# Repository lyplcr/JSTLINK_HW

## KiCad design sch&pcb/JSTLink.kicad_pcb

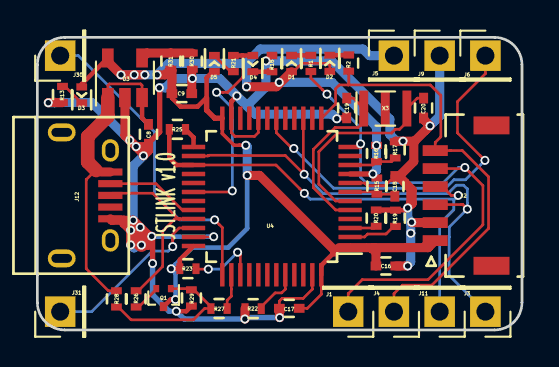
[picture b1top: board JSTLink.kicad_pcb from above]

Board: 2 copper layers, 26.9 x 16.3 mm, 47 parts (1 on the bottom side), 31 nets.

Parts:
C8, C9: 1uF; C_0402
C16, C17: 100nF; C_0402
C18: 10nF; C_0402
C19, C20: 22pF; C_0402
D1, D4: LED-Blue; LED_0402
D2, D5: LED-Green; LED_0402
D3: LED-GREEN; LED_0402
J1, J3, J4, J5, J6, J9, J11, J30, J31: Header_1x1; Pin_Header_Straight_1x01_Pitch2.54mm
J2: JST1.0 1x6; JST_SHL_SM06B-SHLS-TF_06x1.00mm_Angled
J12: USB; USB_Micro-B
LOGO1: LOGO_PINNO_PIC_50x50
Q1: CJ;MMBT3904M; SOT-723
R1, R2, R13, R18, R21: 100k; R_0402
R15, R16, R17, R19, R22, R23, R28: 10k; R_0402
R20: DNP 10k; R_0402
R25, R26, R27: 1k; R_0402
R29: 36k; R_0402
R30, R31: DNP 0R_10nF_RES; R_0402
U3: TPS782; SOT-23-5
U4: STM32F103C8; LQFP-48_7x7mm_Pitch0.5mm
X3: 8MHz; Crystal_SMD_3pin_3.2x1.5mm

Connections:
+3V3: C9.1, C16.1, C17.1, D1.2, D2.2, D3.2, D5.2, J2.1, J5.1, Q1.3, R15.1, R16.2, R23.1, R31.1, U3.5, U4.1, U4.9, U4.24, U4.36, U4.48
/ST-LINK/LED_STLINK: D4.2, R21.2, U4.30
/ST-LINK/NRST: J6.1, U4.18
/ST-LINK/OSC_IN: C19.1, U4.5, X3.1
/ST-LINK/OSC_OUT: C20.1, U4.6, X3.2
/ST-LINK/STM_JTCK: J30.1, U4.37
/ST-LINK/STM_JTMS: J31.1, U4.34
/ST-LINK/STM_RST: C18.1, R15.2, U4.7
/ST-LINK/SWCLK: J2.3, J3.1, U4.15, U4.26
/ST-LINK/SWDIO: J2.4, J11.1, R25.2, U4.27
/ST-LINK/T_SWDIO_IN: R25.1, U4.25
/ST-LINK/USB_DM: J12.2, U4.32
/ST-LINK/USB_DP: J12.3, R26.1, U4.33
/ST-LINK/USB_RENUMn: R27.1, U4.38
/ST-LINK/VBUS: C8.1, J12.1, R28.1, U3.1, U3.3
/ST-LINK/VCP_RX: J1.1, J2.5, R1.2, U4.12
/ST-LINK/VCP_TX: J2.6, J4.1, R2.2, U4.13
GND: C8.2, C9.2, C16.2, C17.2, C18.2, C19.2, C20.2, J2.2, J9.1, J12.5, R13.2, R17.1, R18.2, R19.2, R20.2, R22.1, R29.1, R30.1, U3.2, U4.8, U4.20, U4.23, U4.35, U4.47
unnamed: D1.1, R1.1
unnamed: D2.1, R2.1
unnamed: D3.1, R13.1
unnamed: D4.1, R18.1
unnamed: D5.1, R21.1
unnamed: Q1.1, R27.2, R28.2, R29.2
unnamed: Q1.2, R26.2
unnamed: R16.1, R17.2, U4.10
unnamed: R19.1, U4.2
unnamed: R20.1, U4.3
unnamed: R22.2, U4.44
unnamed: R23.2, U4.39
unnamed: R30.2, R31.2, U3.4

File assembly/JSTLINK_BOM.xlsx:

Id | 代号 | 封装 | 数量 | 名称 | 供应商和REF
1 | C8,C9 | C_0402 | 2 | 1uF
2 | C16,C17 | C_0402 | 2 | 100nF
3 | C18 | C_0402 | 1 | 10nF
4 | C19,C20 | C_0402 | 2 | 22pF
5 | D1,D4 | LED_0402 | 2 | LED-Blue
6 | D2,D5 | LED_0402 | 2 | LED-Green
7 | D3 | LED_0402 | 1 | LED-GREEN
8 | J12 | USB_Micro-B | 1 | USB
10 | Q1 | SOT-723 | 1 | CJ;MMBT3904M
11 | R1,R2,R13,R18,R21 | R_0402 | 5 | 100k
12 | R15,R16,R17,R19,R22,R23,R28 | R_0402 | 7 | 10k
13 | R20 | R_0402 | 1 | DNP 10k
14 | R25,R26,R27 | R_0402 | 3 | 1k
15 | R29 | R_0402 | 1 | 36k
16 | R30,R31 | R_0402 | 2 | DNP 0R_10nF_RES
17 | U3 | SOT-23-5 | 1 | TPS782
18 | U4 | LQFP-48_7x7mm_Pitch0.5mm | 1 | STM32F103C8
19 | X3 | Crystal_SMD_3pin_3.2x1.5mm | 1 | 8MHz
20 | J2 | JST_SHL_SM06B-SHLS-TF_06x1.00mm_Angled | 1 | JST1.0 1x6

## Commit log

2017-04-21 :neckbeard: Added .gitattributes & .gitignore files
2017-04-21 首次打样版本
    1. 完成硬件设计
    2. 首次发出打样
